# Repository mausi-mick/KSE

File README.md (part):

Kleiner , feiner  Kennlinienschreiber

Wozu braucht man einen Kennlinienschreiber ?

Reicht nicht ein Transistortester oder ein Voltmeter?
Für einen ersten Check ist ein Transistortester sehr hilfreich, zumal er auch den Typ des Transistors  und die Pin-Belegung ermitteln und anzeigen kann.

Aber die Ausgabewerte beziehen sich dabei nur auf einen Arbeitspunkt (Kollektorstrom).
Für den Schaltungsentwickler ist es aber oft wichtig, wie sich das Bauteil an verschiedenen
Arbeitspunkten – z.B. Basisströmen – verhält.

Worin unterscheidet sich der hier vorgestellte Kennlineinschreiber von anderen?

    • kompakter Aufbau:                                                                                                 Abmessungen: 8x9x6cm (lxbxh),  Gewicht: < 500 g (inkl. 18650 Lio-Akku).
    • unabhängig von externer Stromversorgung (Akku Betrieb,mit einer 18650 Zelle)
    • ausgelegt für bipolar Transistoren/Dioden, MosFets, J-Fets(incl. Depl.Mode MosFets).
    • Kollektor/Emitterspannung < 12V , 0 ..150mA  optimal für Kleinleistungstransistoren
    • Basisstrom von ca 5µA ... 1000µA mit präziser Konstant-Stromquelle, 
    • Gatespannung  100 mV ...12 V in 100 mV Schritten (änderbar), 
    • einstellbare Strombegrenzung (z.B. Dioden 5mA, 50mA,…)
    • relativ grosses Farbdisplay (3.2“)
    • einfache und schnelle Eingabe über Dreh-Encoder an Interrupt-Pins
    • hohe Genauigkeit und klare Kennlinien dank 12 bit ADC’s / DAC’s
    • diverse Skalen für x (U) und y-(I) Achse : detaillierte Darstellung interessanter Bereiche
    • Direkter Vergleich von Kennlinien (Typen gleicher Polarität oder Komplementärtyp)
    • Anzeige von typischen Werten wie Beta(Ib), V-Threshold,V-Pinch, Idss
    • Bluetooth Schnittstelle (BLE 4.0) für Datentransfer zum PC bzw. Smartphone/ Tablet
    • Datentransfer über USB zur Darstellung der Kurven auf PC mit z.B. Processing.
    • Speichern der Eingabeparameter im internen EEPROM
    • geringer Stromverbrauch: Uce (15V) erst bei Messvorgang zugeschaltet. 
    • Zusatzfunktion: einstellbare  Konstantspannungsquelle 1 mV  bis 12, 00V,> 10 mA
    • Zusatzfunktion: einstellbare Konstanstromquelle von 1µA bis 4000 µA
    • Zusatzfunktion: Treppenstufengenerator für niedrige Frequenzen +4V, ...0V (...-4V) 
    • untergebracht auf 5 Platinen (Kicad) einlagig 
    • relativ niedrige Bauteilkosten

Dieser Kennlinienschreiber basiert auf dem sehr interessanten und gut dokumentierten Projekt von Peter Balch : Transistor Curve Tracer [1], aus dem auch u.a. die Grafik-library leicht modifiziert übernommen wurde.

Ich habe mich dann aber doch ziemlich  - auch vom Konzept her - weit davon entfernt, um eine bessere und rauschärmere Darstellung hinzubekommen mit einem deutlich erweiterten Messbereich ,einer einfachen Bedienung und erweiterter Funktionalität, was sich leider auch im Preis niederschlägt. 
Ich habe die bisherige Bedienung über das Touchpanel eliminiert und mache die Programmsteuerung und Parameteränderungen über zwei Drehencoder, die an den beiden ext. Interrupt-Pins des NANO hängen und so eine schnelle Reaktion ermöglichen. Die Eingabe ist hiermit – gerade bei dem kleinen Display und den vielen Parameterwerten – wesentlich angenehmer und schneller als per Touch. 

Der Nachbau ist wegen einiger SMDs  und der Verdrahtung einiger Platinen  komplexer und daher nicht unbedingt für „Anfänger“ geeignet. Bei einigen Spezial-ICs ist/war auch mit erheblichen Beschaffungszeiten (in Deutschland) zu rechnen.

Basis ist ein Arduino-NANO(Clone), am besten mit vorinstalliertem Opti-Boot Loader [2,3,4], da man dort 1.5 kB mehr freien Flash-Speicher hat, ansonsten hat man nur einige 100 Byte Flash frei.

Anmerkung:
 ATMega328 Board mit vorinstalliertem Opti-Boot-Loader: 
 z.B. Arduino-UNO, Adafruit Metro Mini 328,  oder ein Board mit mehr Flash und Port-Pins (für Erweiterungen): ATMega2560 ).

Anmerkung:
Auch das UNO-Board oder Adafruit Metro-Mini sind hier verwendbar, da ich die zusätzlichen rein analogen Pins des NANO (A6,A7) nicht benutze.

Das Adafruit-Board Metro Mini 328 hat neben der besseren Anordnung der Pins (alle digit.Pins und somit auch Pin13 (SPI-SCK)  auf einer Seite) auch die Möglichkeit, durch eine Lötbrücke die Pegel auf 3.3V zu setzen, sodass man für das Display und das HM-10 BLE-Modul keine Spannungsteiler zur Pegelanpassung benötigt.

Der Mikroprozessor steuert zwei 12bit-DACs (im MCP4822 SPI) für die Uce Versorgung , ausserdem für die Basis/Gate-Ansteuerung einen 12 bit DAC (MCP4725-I2C) an, der über einen DC/DC-Wandler (5 V → 30V) und für den I2C Bus über einen ADUM1250/51 isoliert betrieben wird.  

Dieser total isolierte DAC (Bereich von 1µA bis 4mA, 1µA Schritte, hier nur von 5µA bis 1200µA genutzt für die bipol. Transistoren genutzt) erzeugt den Basisstrom bzw. die Gate-Spannung in der – zum Bauteil / „device“ - passenden Polarität über eine Präzisionskonstantstromquelle.
 
Zugeschaltet wird der Basisstrom (bzw. die Gatespannung)  über elekronische Schalter („Photomos-Relais“) mit niedrigem On-Widerstand und Leckstrom (z.B. TLP222A ).

Neben diesen DACs wird auch ein 12-bit ADC (MCP3402 SPI) zur Messung der Collector-EmitterSpannung und zur am Messwiderstand RS (50 Ohm) abfallenden Spannung (zur Ermittlung des Collector-Stroms) verwandt. Er dient auch zur Überwachung der Akku-Spannung.
Momentan werden nur 3 von den 4 Eingängen des ADC’s genutzt.

Ausserdem versorgt der NANO das bis zu 3.2 Zoll grosse Farb-Display (ILI9341) (an SPI-Bus).

Probleme gab es mit den 4 SPI-Devices wegen der unterschiedlichen Geschwindigkeit, da das Display mit 8 MHz läuft, die DAC’s mit 3.6 MHz und der ADC aber nur mit 2 MHz                      (und der Touch noch langsamer, wird aber in dieser Version nicht genutzt).

Als realisierbare / nicht ganz perfekte Lösung speichere ich maximal 320-Messwerte pro eingestelltem Basisstrom in einer Tabelle mit SPI-Speed 2 MHz ab.
Anschliessend erhöhe ich die SPI-Speed auf 8MHz für das Display und
 gebe die Tabellenwerte auf dem Display aus, um dann wieder – mit reduzierter SPI-Speed - die nächsten 320 Messwerte zum nächsten Basisstrom zu speichern.

Die Spannung Uc wird über die beiden DACs des MCP4822 erzeugt, wobei DAC-B nur
die Werte (0V, 2V,4V ...10V) am Opamp TCA0372 ausgibt,
DAC-A erzeugt die Zwischenwerte von 0.0mV, 0.5mV, 1.0mV.,..2000mV.
Sie werden dann zu den aus DC-B erzeugten Werten addiert (zwei invertierende Verstärker hintereinandergeschaltet) , sodass insgesamt der Bereich von
0V bis 12V in 0.5mV – Schritten mit sehr guter Linearität erzeugt werden kann.
Diese Auflösung ist zwar etwas übertrieben, bei kleinen Spannungswerten (z.B. Kennlinie von Shottky-Dioden oder im Anfangsbereich der Kurven von bipolar bzw. Feldeffekttransistoren) bringt das aber was, auch wird durch eine Art „Oversampling“ der Mittelwert der Messungen zum gleichen x_Wert gebildet

Der Summierverstärker TCA0372 mit Verstärkung +1 für DAC_A und Verstärkung +10 für DAC_B ist in Abbildung 1 skizziert.
Da der TCA0372 kein Rail-to Rail Vertärker ist, benötigt er eine negative Hilfsspannung: 
 aus den +15V wird mithilfe eines kleinen Spannungswandlers (LMO78-5-.5 )  -5V erzeugt. 
Damit erhält man auch in Nullpunktsnähe saubere Kurven, gerade die 1, 2, 3V Skalen profitieren davon.

Stromversorgung

Versorgt wird der Kennlinienschreiber aus einer einzelnen Lion-Akku-Zelle (18650).
Es werden zwei Spannungen benötigt:
   5V für  Adafruit Metro mini bzw. 7,5V Arduino NANO) , an der auch das Diplay und die KonstantStromquelle hängen, und ca.
 15V zur Versorgung des TCA0372-Verstärkerboards (Uce).

Die zuerst untersuchte Lösung mit zwei MT3608 Modulen funktionierte stabil nur für die 15V Versorgung, bei der Microprocessorversorgung brach die Spannung bereits bei einer Akkuspannung von 3.9V ein.

Die Qualität der MT3608-Module  – neben der riskanten Inbetriebnahme (siehe unten) – ist aber sehr unterschiedlich, sodass ich auch eher andere Module verwenden würde.
Die ICs MT3608, SDB628 und SX1308 scheinen – auch vom Datenblatt – identisch zu sein.
Aber die Module haben unterschiedliches Layout und wohl auch unterschiedliche Bestückung.

Die Kondensatoren C1 C2 sollten 22µF haben, bei den von mir untersuchten Modulen lagen sie 
unter 10 µF.

Es funktioniert sehr gut mit einem kleinen SX1308-Modul, bei dem bei mir aber ein SDB628 StepUp-Wandler IC aufgelötet war. 

Das Modul ist ähnlich wie das MT3608-Modul aufgebaut, aber
niederohmiger: 
10 k anstelle 100k Trimmer und 200 Ohm gegen Masse anstelle 2.2k. [9]

Es ist bei 15V mit mehr als 150mA belastbar und funktioniert bereits ab ca 2.7 V.
Es ist auch für die 5V / 7,5V Vesrorgung sehr gut geeignet.

Für die 5 bzw. 7.5V verwende ich momentan ein kleines Modul mit festen Spannungswerten  (5V,8V,9V,12V). Es ist wohl ein SDB628 verbaut ( identisch mit MT3608 / SX1308?)  das Modul funktioniert sogar  bis unter 3V Eingansspannung. [10]

Anmerkung MT3608:
Etwas kritisch ist die Einstellung/Inbetriebnahme, da der Schleifer des 10-Gang-Trimmers direkt mit dem FB (Feedback-Pin 3)  verbunden ist und - am oberen Anschlag  -  die Ausgansspannung direkt mit FB  verbunden ist, der wohl nur 0.6V ? verträgt.
Man sollte also vor Anlegen der Eingansspannung den Regler mit ein einigen Umdrehungen aus der oberenAnschlagsposition bringen (und zwar nach höheren Ausgansspannungswerten , d.h. nach links drehen   chinesische Logik ??)   [5,6],

Um Energie zu sparen, wird die 15V Versorgung erst aktiviert, wenn die Kurven aufbereitet werden.
Die 7.5V / 5V  stehen nach Einschalten für das Microprocessor Board gleich zur Verfügung, an dem u.a.  das Display und die Konstanstromquelle hängen, die aber weniger als 1W benötigt.

Beim Einschalten sind die Ströme - auch wegen der Kondensatoren - deutlich höher.

Das Adafruit Board braucht wegen eines besseren LD-Reglers , auch reichen hier 5V am  herausgeführten USB-Eingang.
9],[10],[11]

Testen von Bauteilen

Nach diesem technischen Überblick mal etrwas mehr zum Test-Ablauf:

Nach dem Einschalten erscheint auf dem Display der Startbildschirm , auf dem an der linken Seite nur drei grosse Icons  aufleuchten mit Auswahlfeldern (Buttons) für:
    •  bipolar Transistoren (inclusive Dioden)
    •  Mosfets
    •  Junction-Fets (incl. n-Depletion-Mode-Mosfets)
      
die über einen Drehencoder angesteuert werden.
Die Aktivierung einer Schaltfläche erfolgt durch Drehen des 2. Encoders.
Daraufhin werden im oberen Bereich zwei Schaltflächen („P“ bzw „N“) zum Starten des Messvorgangs angezeigt, vorher sollte man aber die unterhalb in zwei Spalten dargestellten Parameter begutachten  und eventuell modifizieren.
Im mittleren Display Bereich an der linken Seite  die Parameter: 

    •  min:   minimaler Wert (Basisstrom bzw. Gatespannung), mit dem der Messvorgang gestartet werden soll
    •  incr: Schrittweite, mit der Basisstrom bzw. Gatespannung erhöht werden soll
    •  max:  maximal datzustellende  Basisstrom bzw. Gatespannungs-Kurve

Die Basisströme werden in µA eingetragen, die Gatespannung in 100mV Schritten.
 Von einer Diode wird dann ausgegangen, wenn bei  „bipolar“ das Feld  incr: auf 0 gesetzt wird.

Am rechten Rand des Displays werden folgende Parameter angezeigt:

    •   Bluet/CCS: Transfer der Daten mit BLE 4.0 an PC bzw Smartphone,  bzw.    Konstantspannungs-Konstantspannungs-Betrieb
    •   x-scale[V]:    Länge der x-Skala  ( 1V,  2V,  3V,  4V,  6V,  12V)
    •   y-scale[mA]  Höhe   der y-Skala ( 2 mA, 5 mA, 10 mA, 20 mA, 50 mA, 100 mA)
Anmerkung: 
 Feld Bluet/CCS = 0         Ausgabe der Kennliniendaten 
                            = 1        Ausgabe der Kennliniendaten auch über Bluetooth an Smartphone etc. 
                            = 2        Umschalten auf Konstantspannungsquellen-Betrieb
                            = 3        Umschalten auf  Konstantstromquellen-Betrieb   
                            = 4,5 ,6 Treppenstufengenerator. 
                            
Die Verwaltung der Parameter erfolgt ähnlich wie beim Startbildschirm beschrieben, zwischen den Feldern springt man durch Drehen des Encoders 2, Auswahl eines Paramters durch mit dem anderen Encoder, ändern der Parameter duch Encoder-Drehung, Speichern/Verlassen des Parameters durch den andren Encoder.

Ist man mit den Einstellungen zufrieden, startet man den Messvorgang / Kurven durch Positionieren mit dem  Encoder auf Feld „P“  (für p-Devices) bzw. “N“ (für n-Devices)  
Hier hat man eine geringe Wartezeit zum Aktivieren, in der man nochmals die Parameter prüfen sollte. In dieser Wartephase blinken die aktivierten Felder P  bzw N. Durch drehen des anderen Encoders startet man dann den Messvorgang.

Erst jetzt sieht man die ausgewählten Skalen und im oberen Bereich das ausgewählte Device inclusive Icon.

Die Kurven werden vom x-y-0-Punkt aufgebaut und zusätzliche Daten (wie z.B. beta/hfe beim npn/pnp und der Basisstrom/Gatespannung )  am Ende der Kurven eingetragen.

Am Ende der Messung bleibt der Bildschirm mit den dargestellten Kurve stehen und es erscheint links oben eine Anfrage / Aufforderung in zeitlichem Abstand :

    •   ob man die Messung beenden will  („Stop ?“)
    •   ob man die Messung fortsetzen will mit geänderten Parametern  („Param ?“)
    •   ob man das gerade dargestellte Bauteil mit einem Bauteil gleicher Polarität vergleichen will („Compare ?“) 
    •   ob man das gerade dargestellete Bauteil mit einem Bauteil anderer Polarität vergleichen will („Complem. ?“)  (komplementär-Typ z.B. antiparallele Diode)

Die Auswahl erfolgt wieder durch Encoderdrehung zu dem gerade angezeigten Aufforderung.

Anmerkung:

Will man z.B. die Kennlinien von einem n-Device mit einem p-Device vergleichen, ermittelt man zuerst normal die Kennlinien des n-Devices, tauscht das n gegen das p-Device in der Textool Messfassung und startet den Vergleich 
durch Auswahl des Feldes „Complementary“ mit dem Encoder .

Es werden die Kennlinien des p-Devices zusätzlich in einer anderen Farbe auf dem Display dargestellt („Komplementärtyp“).

Vergleich von Komponenten gleicher Polarität erfolgt entsprechend 
durch Auswahl des Feldes „Compare“.

   Speicherung geänderter Parameter-im internen EEPROM

Die festgelegten Parameter werden beim Start der Kurven im internen EEPROM hinterlegt , 
sodass man auch beim Einschalten des Geräts die letzt eingegebenen Parameter angezeigt bekommt. 

Im EEPROM sind dafür folgende Adressen belegt:

    •   0: Transistor-Typ  0: bipolar,
    •   1: Bluetooth : 1=on, 0=off
    •   2: x-Skala: 1,2,3,4,6,12
    •   3 y-Skala: 2,5,10,20,50,100 mA
    •   4: minimaler Basisstrom bipolar-Transistor
    •   6: maximaler Basisstrom bipolar-Transistor 
    •   8: increment Basisstrom bipolar-Transistor 
    • 10: minimale Stepweite für Eingabe  min: ( Feld 4 )
    • 12: minimale StepWeite für Eingabe max: ( Feld 6 )
    • 14: minimale StepWeite für Eingabe incr:: ( Feld 8 )

    •   20: Transistor-Typ  1:  Mosfet
    •   21: Bluetooth : 1=on, 0=off
    •   22: x-Skala: 1,2,3,4,6,12
    •   23 y-Skala: 2,5,10,20,50,100 mA
    •   24: minimaler Gatespannung Mosfet
    •   26: maximaler GatespannungMosfet 
    •   28: increment Gatespannung Mosfet 
    •   30: minimale Stepweite für Eingabe  min: ( Feld 24 )
    •   32: minimale StepWeite für Eingabe max: ( Feld 26 )
    •   34: minimale StepWeite für Eingabe incr:: ( Feld 28 )

    •   40: Transistor-Typ  2:  J-Fet 
    •   41: Bluetooth : 1=on, 0=off
    •   42: x-Skala: 1,2,3,4,6,12
    •   43 y-Skala: 2,5,10,20,50,100 mA
    •   44: minimaler  Gatespannung J-Fet
    •   46: maximaler Gatespannung-J-Fet 
    •   48: increment  Gatespannung J-Fet 
    •   50: minimale Stepweite für Eingabe  min: ( Feld 44 )
    •   52: minimale StepWeite für Eingabe max: ( Feld 46 )
    •   54: minimale StepWeite für Eingabe incr:: ( Feld 48 )

Ausserdem kann man den Bauteil-Namen (z.B. BC548C  oder auch andere Informationen) im internen EEProm ab Adresse 100/101 hinterlegen: 

    •   100: Länge des Textfeldes 
    •   101: Text 1. Byte
    •   102: Text 2. Byte
    •  ...
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
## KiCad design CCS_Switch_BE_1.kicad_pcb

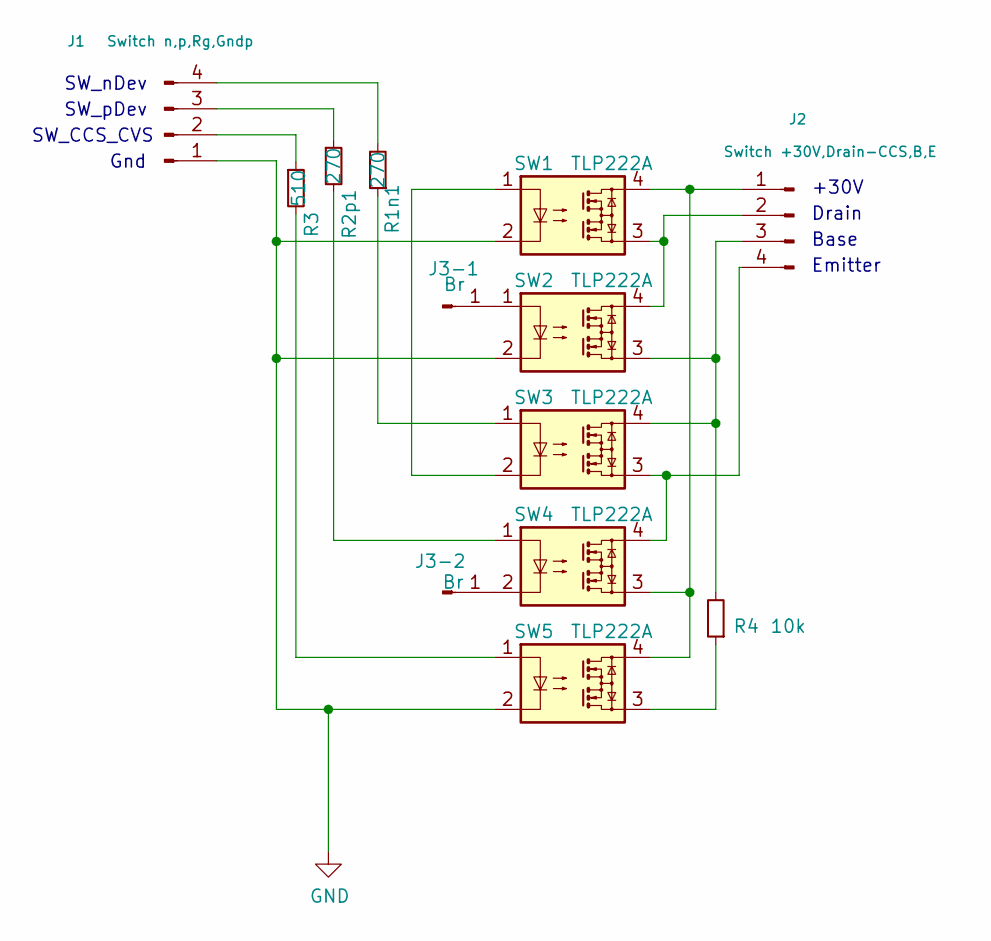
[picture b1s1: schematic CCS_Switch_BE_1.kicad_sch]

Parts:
J1: Switch n,p,Rg,Gndp; PinHeader_1x04_P2.54mm_Vertical
J2: Switch +30V,Drain-CCS,B,E; PinHeader_1x04_P2.54mm_Vertical
J3-1, J3-2: Br; PinHeader_1x01_P2.54mm_Vertical
R1n1, R2p1: 270; R_1206_3216Metric_Pad1.30x1.75mm_HandSolder
R3: 510; R_1206_3216Metric_Pad1.30x1.75mm_HandSolder
R4: 10k; R_Axial_DIN0207_L6.3mm_D2.5mm_P10.16mm_Horizontal
SW1, SW2, SW3, SW4, SW5: TLP222A; DIP-4_W7.62mm

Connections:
GND: J1.1, SW1.2, SW2.2, SW5.2
unnamed: J1.2, R3.1
unnamed: J1.3, R2p1.1
unnamed: J1.4, R1n1.2
unnamed: J2.1, SW1.4, SW4.3, SW5.4
unnamed: J2.2, SW1.3, SW2.4
unnamed: J2.3, R4.2, SW2.3, SW3.4
unnamed: J2.4, SW3.3, SW4.4
unnamed: J3-1.1, SW2.1
unnamed: J3-2.1, SW4.2
unnamed: R1n1.1, SW3.1
unnamed: R2p1.2, SW4.1
unnamed: R3.2, SW5.1
unnamed: R4.1, SW5.3
unnamed: SW1.1, SW3.2

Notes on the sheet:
Base
SW_pDev
SW_CCS_CVS
SW_nDev
+30V
Drain
Emitter
Gnd

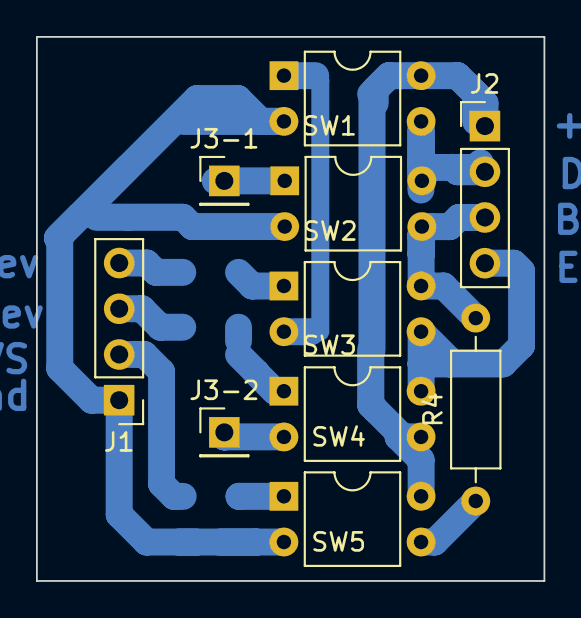
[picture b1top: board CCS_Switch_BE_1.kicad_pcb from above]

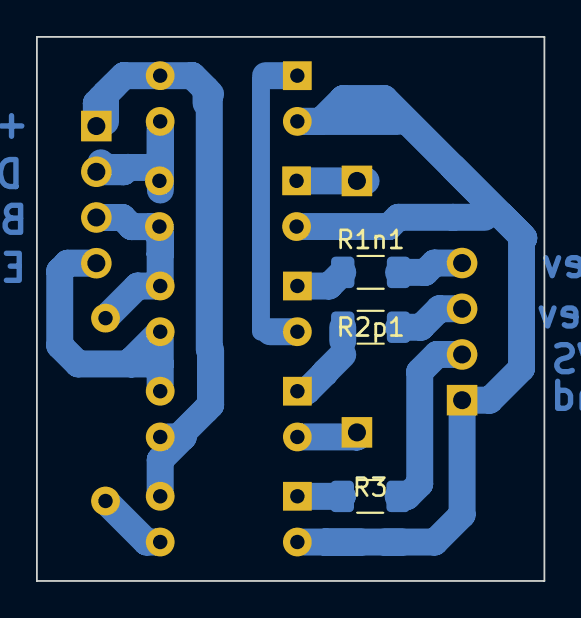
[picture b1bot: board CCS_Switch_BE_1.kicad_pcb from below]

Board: 2 copper layers, 28.2 x 30.2 mm, 13 parts (3 on the bottom side), 15 nets.

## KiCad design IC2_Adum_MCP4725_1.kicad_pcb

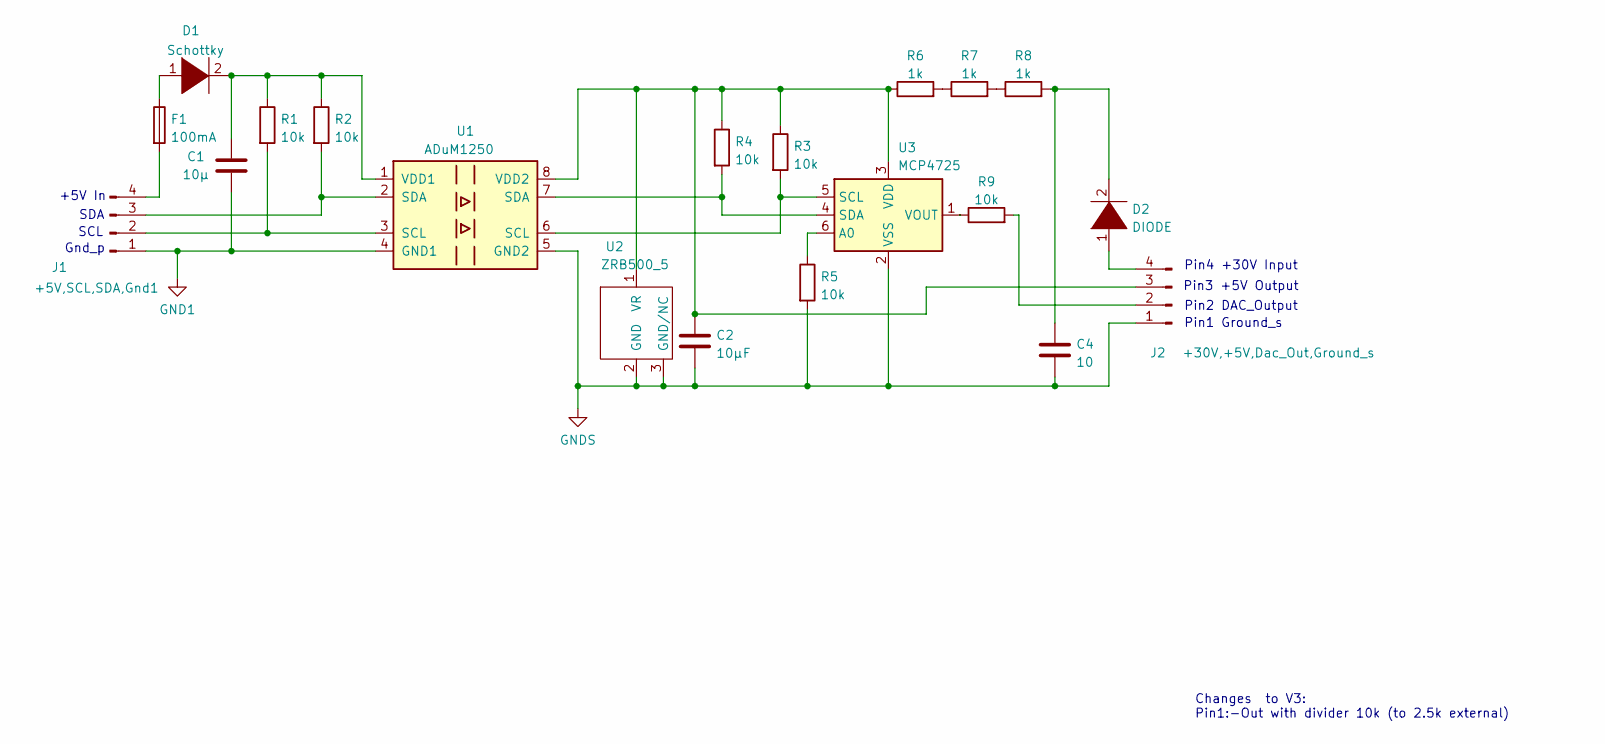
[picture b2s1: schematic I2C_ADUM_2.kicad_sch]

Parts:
C1: 10µ; C_1206_3216Metric_Pad1.33x1.80mm_HandSolder
C2: 10µF; C_1210_3225Metric_Pad1.33x2.70mm_HandSolder
C4: 10; C_1210_3225Metric_Pad1.33x2.70mm_HandSolder
D1: Schottky; D_1206_3216Metric_Pad1.42x1.75mm_HandSolder
D2: DIODE; D_0805_2012Metric_Pad1.15x1.40mm_HandSolder
F1: 100mA; Fuse_1206_3216Metric_Pad1.42x1.75mm_HandSolder
J1: +5V,SCL,SDA,Gnd1; PinHeader_1x04_P2.54mm_Vertical
J2: +30V,+5V,Dac_Out,Ground_s; PinHeader_1x04_P2.54mm_Vertical
R1, R2, R3, R4, R5, R9: 10k; R_1206_3216Metric_Pad1.30x1.75mm_HandSolder
R6, R7, R8: 1k; R_1206_3216Metric_Pad1.30x1.75mm_HandSolder
U1: ADuM1250; SOIC-8_3.9x4.9mm_P1.27mm
U2: ZRB500_5; SOT-23-3
U3: MCP4725; SOT-23-6

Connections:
GND1: C1.2, J1.1, U1.4 (GND1)
GNDS: C2.2, C4.2, J2.1, R5.2, U1.5 (GND2), U2.2 (GND), U2.3 (GND/NC), U3.2 (VSS)
unnamed: C1.1, D1.2 (A), R1.1, R2.1, U1.1 (VDD1)
unnamed: C2.1, J2.3, R3.1, R4.1, R6.1, U1.8 (VDD2), U2.1 (VR), U3.3 (VDD)
unnamed: C4.1, D2.2 (A), R8.2
unnamed: D1.1 (K), F1.1
unnamed: D2.1 (K), J2.4
unnamed: F1.2, J1.4
unnamed: J1.2, R1.2, U1.3 (SCL)
unnamed: J1.3, R2.2, U1.2 (SDA)
unnamed: J2.2, R9.2
unnamed: R3.2, U1.6 (SCL), U3.5 (SCL)
unnamed: R4.2, U1.7 (SDA), U3.4 (SDA)
unnamed: R5.1, U3.6 (A0)
unnamed: R6.2, R7.1
unnamed: R7.2, R8.1
unnamed: R9.1, U3.1 (VOUT)

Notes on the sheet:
Pin2 DAC_Output
Changes to V3: Pin1:-Out with divider 10k (to 2.5k external)
+5V In
Pin3 +5V Output
Gnd_p
SDA
Pin1 Ground_s
SCL
Pin4 +30V Input

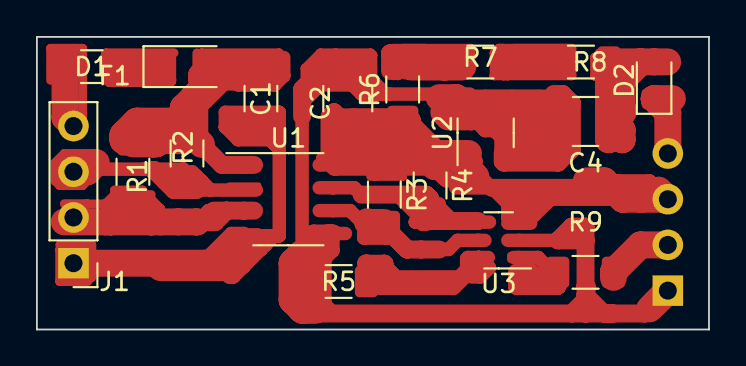
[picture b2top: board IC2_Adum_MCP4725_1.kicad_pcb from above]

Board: 2 copper layers, 37.3 x 16.3 mm, 20 parts (1 on the bottom side), 17 nets.

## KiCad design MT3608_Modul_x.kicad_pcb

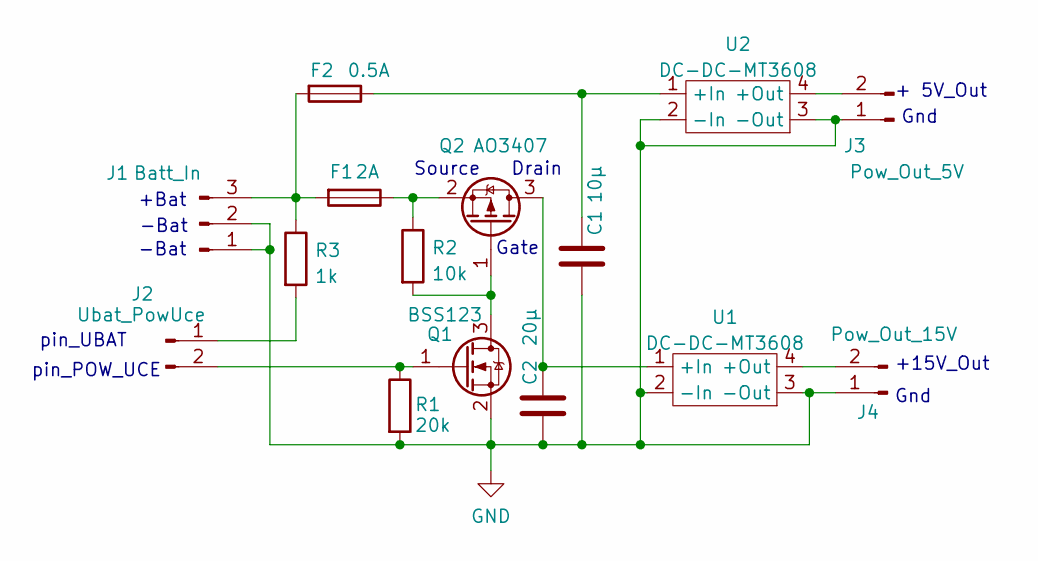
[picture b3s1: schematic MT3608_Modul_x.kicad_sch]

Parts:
C1: 10µ; C_1206_3216Metric_Pad1.33x1.80mm_HandSolder
C2: 20µ; C_1210_3225Metric_Pad1.33x2.70mm_HandSolder
F1: 2A; Fuse_1206_3216Metric_Pad1.42x1.75mm_HandSolder
F2: 0.5A; Fuse_1206_3216Metric_Pad1.42x1.75mm_HandSolder
J1: Batt_In; PinHeader_1x03_P2.54mm_Horizontal
J2: Ubat_PowUce; PinHeader_1x02_P2.54mm_Vertical
J3: Pow_Out_5V; PinHeader_1x02_P2.54mm_Vertical
J4: Pow_Out_15V; PinHeader_1x02_P2.54mm_Vertical
Q1: BSS123; SOT-23
Q2: AO3407; SOT-23
R1: 20k; R_1206_3216Metric_Pad1.30x1.75mm_HandSolder
R2: 10k; R_1206_3216Metric_Pad1.30x1.75mm_HandSolder
R3: 1k; R_1206_3216Metric_Pad1.30x1.75mm_HandSolder
U1, U2: DC-DC-MT3608

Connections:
GND: C1.2, C2.2, J1.1, J1.2, J3.1, J4.1, Q1.2 (S), R1.2, U1.2 (-In), U1.3 (-Out), U2.2 (-In), U2.3 (-Out)
unnamed: C1.1, F2.1, U2.1 (+In)
unnamed: C2.1, Q2.3 (D), U1.1 (+In)
unnamed: F1.1, Q2.2 (S), R2.1
unnamed: F1.2, F2.2, J1.3, R3.1
unnamed: J2.1, R3.2
unnamed: J2.2, Q1.1 (G), R1.1
unnamed: J3.2, U2.4 (+Out)
unnamed: J4.2, U1.4 (+Out)
unnamed: Q1.3 (D), Q2.1 (G), R2.2

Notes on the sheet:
Drain
pin_UBAT
-Bat
Source
+Bat
pin_POW_UCE
+15V_Out
Gnd
Gate
+ 5V_Out

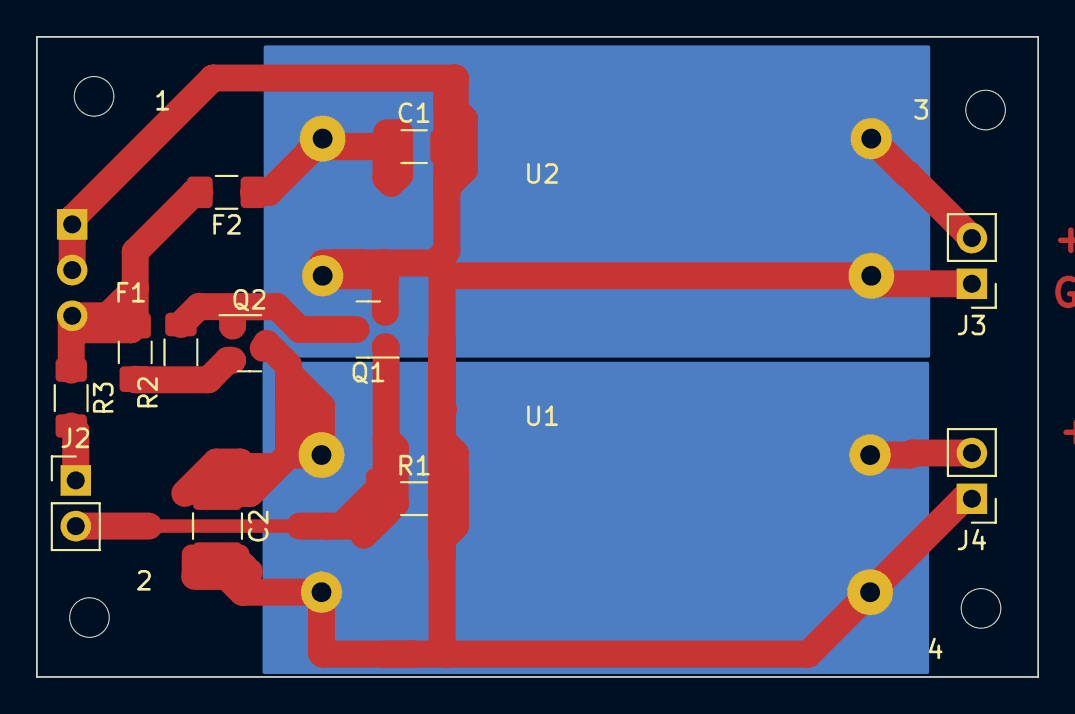
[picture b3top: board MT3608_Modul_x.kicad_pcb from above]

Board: 2 copper layers, 55.6 x 35.6 mm, 19 parts (1 on the bottom side), 10 nets.

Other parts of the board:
1, 2, 3, 4: MH_M2; MountingHole_2.2mm_M2

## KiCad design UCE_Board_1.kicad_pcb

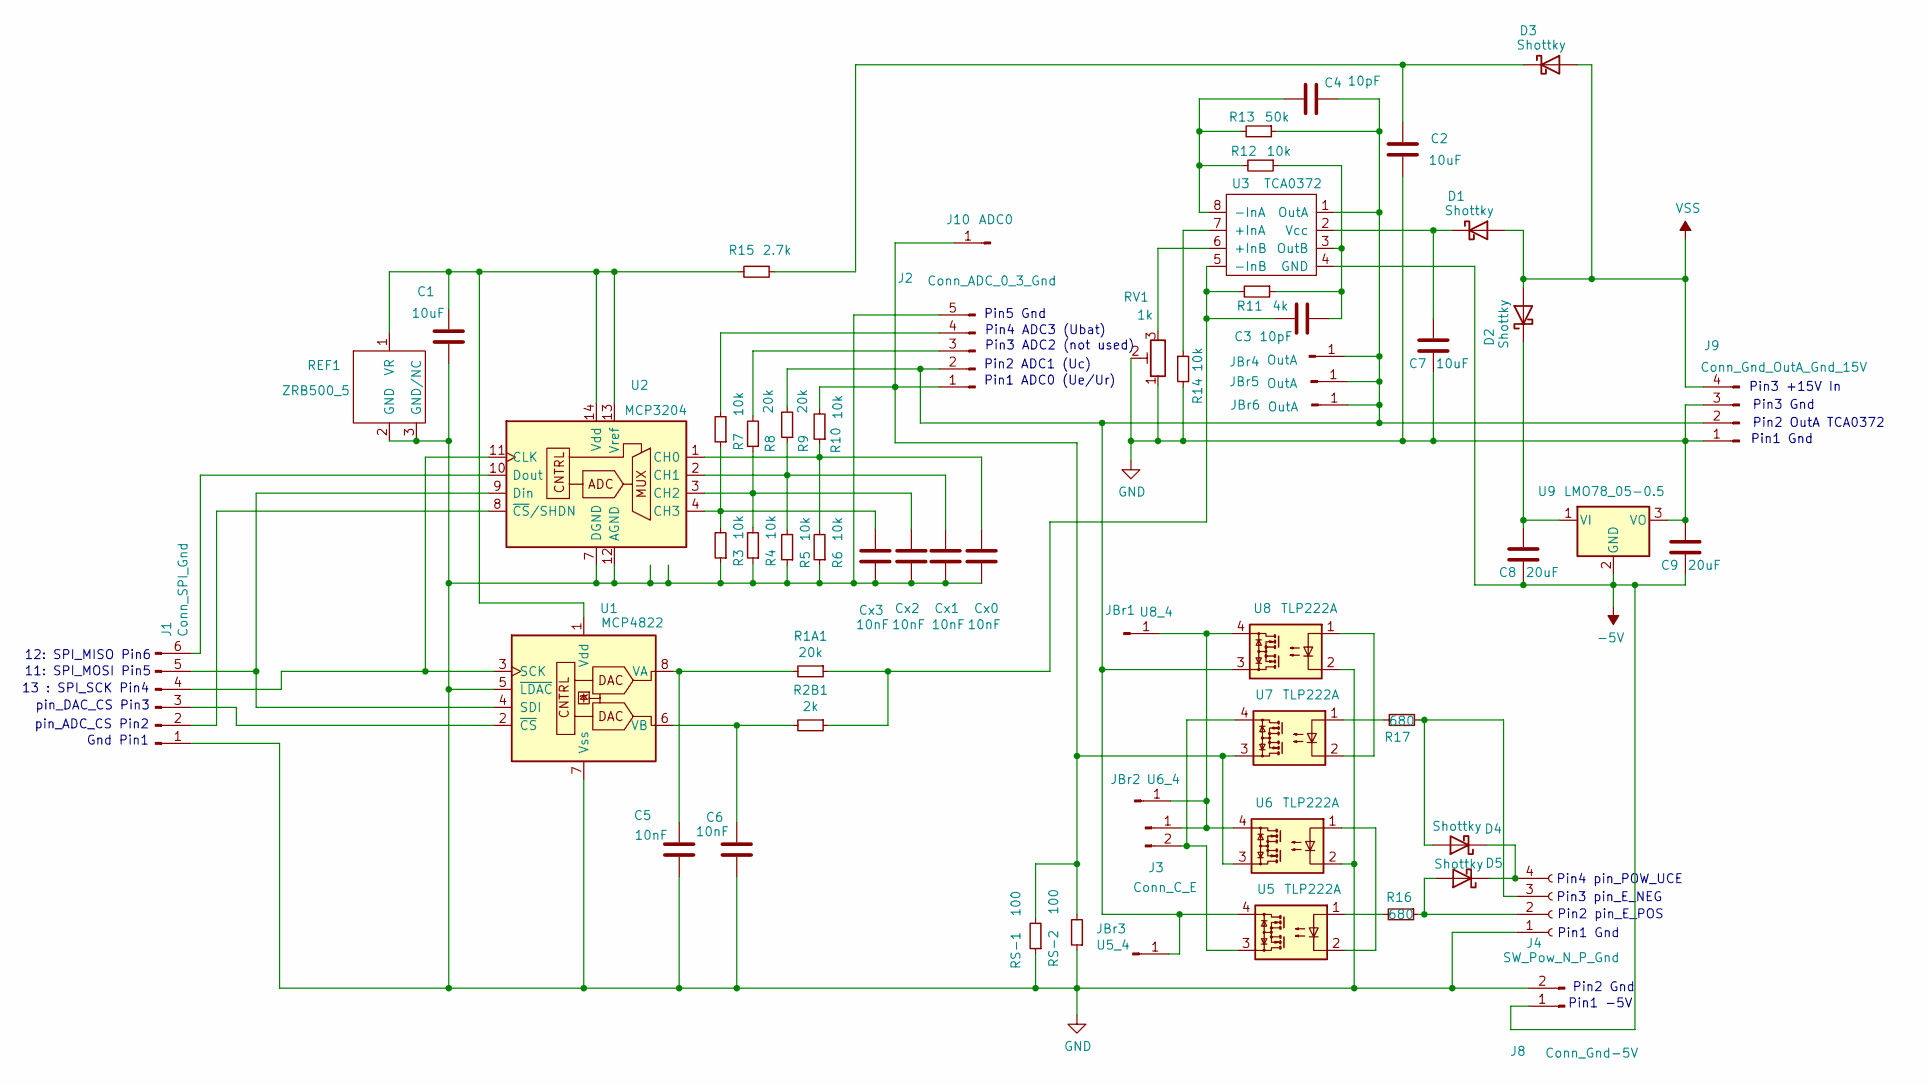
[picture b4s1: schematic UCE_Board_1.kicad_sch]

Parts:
C1: 10uF; C_1210_3225Metric_Pad1.33x2.70mm_HandSolder
C2: 10uF; C_1812_4532Metric_Pad1.57x3.40mm_HandSolder
C3: 10pF; C_Axial_L5.1mm_D3.1mm_P7.50mm_Horizontal
C4: 10pF; C_Axial_L3.8mm_D2.6mm_P7.50mm_Horizontal
C5, C6: 10nF; C_1206_3216Metric_Pad1.33x1.80mm_HandSolder
C7: 10uF; C_1206_3216Metric_Pad1.33x1.80mm_HandSolder
C8, C9: 20uF; C_1812_4532Metric_Pad1.57x3.40mm_HandSolder
Cx0, Cx1, Cx2, Cx3: 10nF; C_0805_2012Metric_Pad1.18x1.45mm_HandSolder
D1, D2, D3: Shottky; D_1206_3216Metric_Pad1.42x1.75mm_HandSolder
D4, D5: Shottky; D_0603_1608Metric_Pad1.05x0.95mm_HandSolder
J1: Conn_SPI_Gnd; PinHeader_1x06_P2.54mm_Horizontal
J2: Conn_ADC_0_3_Gnd; PinHeader_1x05_P2.54mm_Vertical
J3: Conn_C_E; PinHeader_1x02_P2.54mm_Horizontal
J4: SW_Pow_N_P_Gnd; PinHeader_1x04_P2.54mm_Horizontal
J8: Conn_Gnd-5V; PinHeader_1x02_P2.54mm_Vertical
J9: Conn_Gnd_OutA_Gnd_15V; PinHeader_1x04_P2.54mm_Horizontal
J10: ADC0; PinHeader_1x01_P2.54mm_Vertical
JBr1: U8_4; PinHeader_1x01_P2.54mm_Vertical
JBr2: U6_4; PinHeader_1x01_P2.54mm_Vertical
JBr3: U5_4; PinHeader_1x01_P2.54mm_Vertical
JBr4, JBr5, JBr6: OutA; PinHeader_1x01_P2.54mm_Vertical
R1A1, R8, R9: 20k; R_1206_3216Metric_Pad1.30x1.75mm_HandSolder
R2B1: 2k; R_1206_3216Metric_Pad1.30x1.75mm_HandSolder
R3, R4, R5, R6, R7, R10: 10k; R_1206_3216Metric_Pad1.30x1.75mm_HandSolder
R11: 4k; R_Axial_DIN0207_L6.3mm_D2.5mm_P10.16mm_Horizontal
R12: 10k; R_Axial_DIN0207_L6.3mm_D2.5mm_P10.16mm_Horizontal
R13: 50k; R_Axial_DIN0207_L6.3mm_D2.5mm_P10.16mm_Horizontal
R14: 10k; R_Axial_DIN0207_L6.3mm_D2.5mm_P15.24mm_Horizontal
R15: 2.7k; R_Axial_DIN0207_L6.3mm_D2.5mm_P10.16mm_Horizontal
R16, R17: 680; R_Axial_DIN0207_L6.3mm_D2.5mm_P10.16mm_Horizontal
REF1: ZRB500_5; SOT-23
RS-1, RS-2: 100; R_Axial_DIN0207_L6.3mm_D2.5mm_P10.16mm_Horizontal
RV1: 1k; Potentiometer_ACP_CA9-H2,5_Horizontal
U1: MCP4822; DIP-8_W7.62mm_LongPads
U2: MCP3204; DIP-14_W7.62mm
U3: TCA0372; DIP-8_W7.62mm_LongPads
U5, U6, U7, U8: TLP222A; DIP-4_W7.62mm
U9: LMO78_05-0.5; TO-220-3_Vertical

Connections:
-5V: C8.2, C9.2, J8.1, U3.4 (GND), U9.2 (GND)
GND: C1.2, C2.2, C5.1, C6.1, C7.2, C9.1, Cx0.1, Cx1.1, Cx2.1, Cx3.1, J1.1, J2.5, J4.1, J8.2, J9.1, J9.3, R3.1, R4.1, R5.1, R6.1, R14.2, REF1.2 (GND), REF1.3 (GND/NC), RS-1.1, RS-2.1, RV1.1, RV1.2, U1.5 (~LDAC), U1.7 (Vss), U2.5 (NC), U2.6 (NC), U2.7 (DGND), U2.12 (AGND), U6.2, U8.2, U9.3 (VO)
unnamed: C1.1, R15.2, REF1.1 (VR), U1.1 (Vdd), U2.13 (Vref), U2.14 (Vdd)
unnamed: C2.1, D3.1 (K), R15.1
unnamed: C3.1, R11.1, R12.1, U3.3 (OutB)
unnamed: C3.2, R1A1.1, R2B1.1, R11.2, U3.5 (-InB)
unnamed: C4.1, J2.2, J9.2, JBr3.1, JBr4.1, JBr5.1, JBr6.1, R9.2, R13.1, U3.1 (OutA), U5.4, U8.3
unnamed: C4.2, R12.2, R13.2, U3.8 (-InA)
unnamed: C5.2, R1A1.2, U1.8 (VA)
unnamed: C6.2, R2B1.2, U1.6 (VB)
unnamed: C7.1, D1.1 (K), U3.2 (Vcc)
unnamed: C8.1, D2.1 (K), U9.1 (VI)
unnamed: Cx0.2, R6.2, R10.1, U2.1 (CH0)
unnamed: Cx1.2, R5.2, R9.1, U2.2 (CH1)
unnamed: Cx2.2, R4.2, R8.1, U2.3 (CH2)
unnamed: Cx3.2, R3.2, R7.1, U2.4 (CH3)
unnamed: D4.1 (K), D5.1 (K), J4.4
unnamed: D4.2 (A), J4.3, R17.1
unnamed: D5.2 (A), J4.2, R16.1
unnamed: J1.2, U2.8 (~CS/SHDN)
unnamed: J1.3, U1.2 (~CS)
unnamed: J1.4, U1.3 (SCK), U2.11 (CLK)
unnamed: J1.5, U1.4 (SDI), U2.9 (Din)
unnamed: J1.6, U2.10 (Dout)
unnamed: J2.3, R8.2
unnamed: J2.4, R7.2
unnamed: J3.1, JBr1.1, JBr2.1, U6.4, U8.4
unnamed: J3.2, U5.3, U7.4
unnamed: J2.1, J10.1, R10.2, RS-1.2, RS-2.2, U6.3, U7.3
unnamed: R14.1, U3.7 (+InA)
unnamed: R16.2, U5.1
unnamed: R17.2, U7.1
unnamed: RV1.3, U3.6 (+InB)
unnamed: U5.2, U6.1
unnamed: U7.2, U8.1
VSS: D1.2 (A), D2.2 (A), D3.2 (A), J9.4

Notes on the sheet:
pin_ADC_CS Pin2
Pin1 Gnd
Pin5 Gnd
Gnd Pin1
Pin3 pin_E_NEG
Pin2 OutA TCA0372
Pin4 pin_POW_UCE
12: SPI_MISO Pin6
Pin2 ADC1 (Uc)
pin_DAC_CS Pin3
Pin2 pin_E_POS
Pin3 ADC2 (not used)
Pin2 Gnd
Pin1 ADC0 (Ue/Ur)
Pin3 +15V In
Pin1 -5V
Pin3 Gnd
11: SPI_MOSI Pin5
Pin4 ADC3 (Ubat)
13 : SPI_SCK Pin4

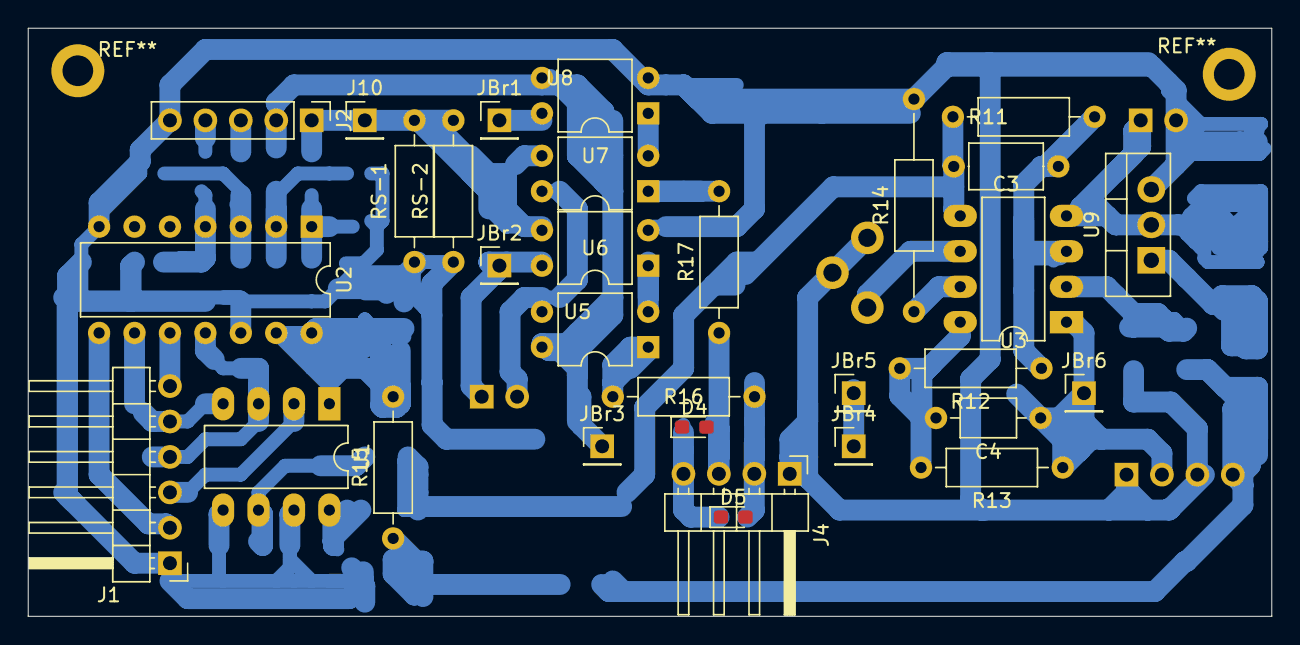
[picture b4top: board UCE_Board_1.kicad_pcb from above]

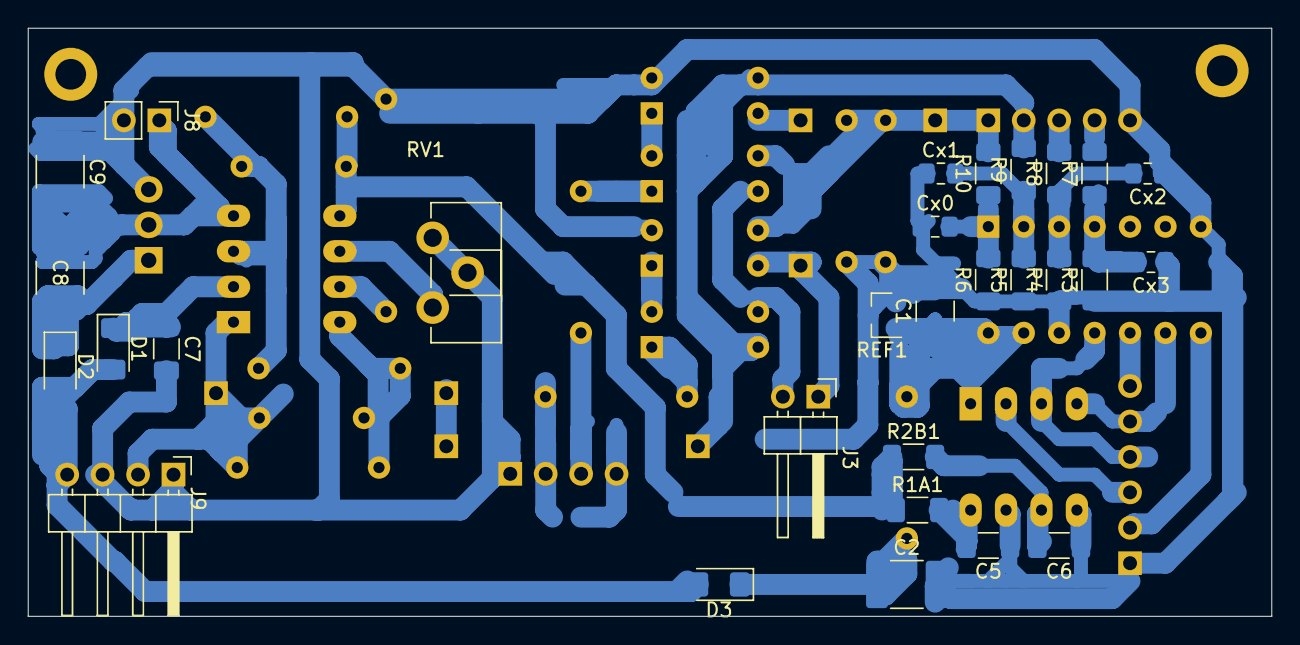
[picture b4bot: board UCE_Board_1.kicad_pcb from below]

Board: 2 copper layers, 89.2 x 42.2 mm, 60 parts (29 on the bottom side), 36 nets.

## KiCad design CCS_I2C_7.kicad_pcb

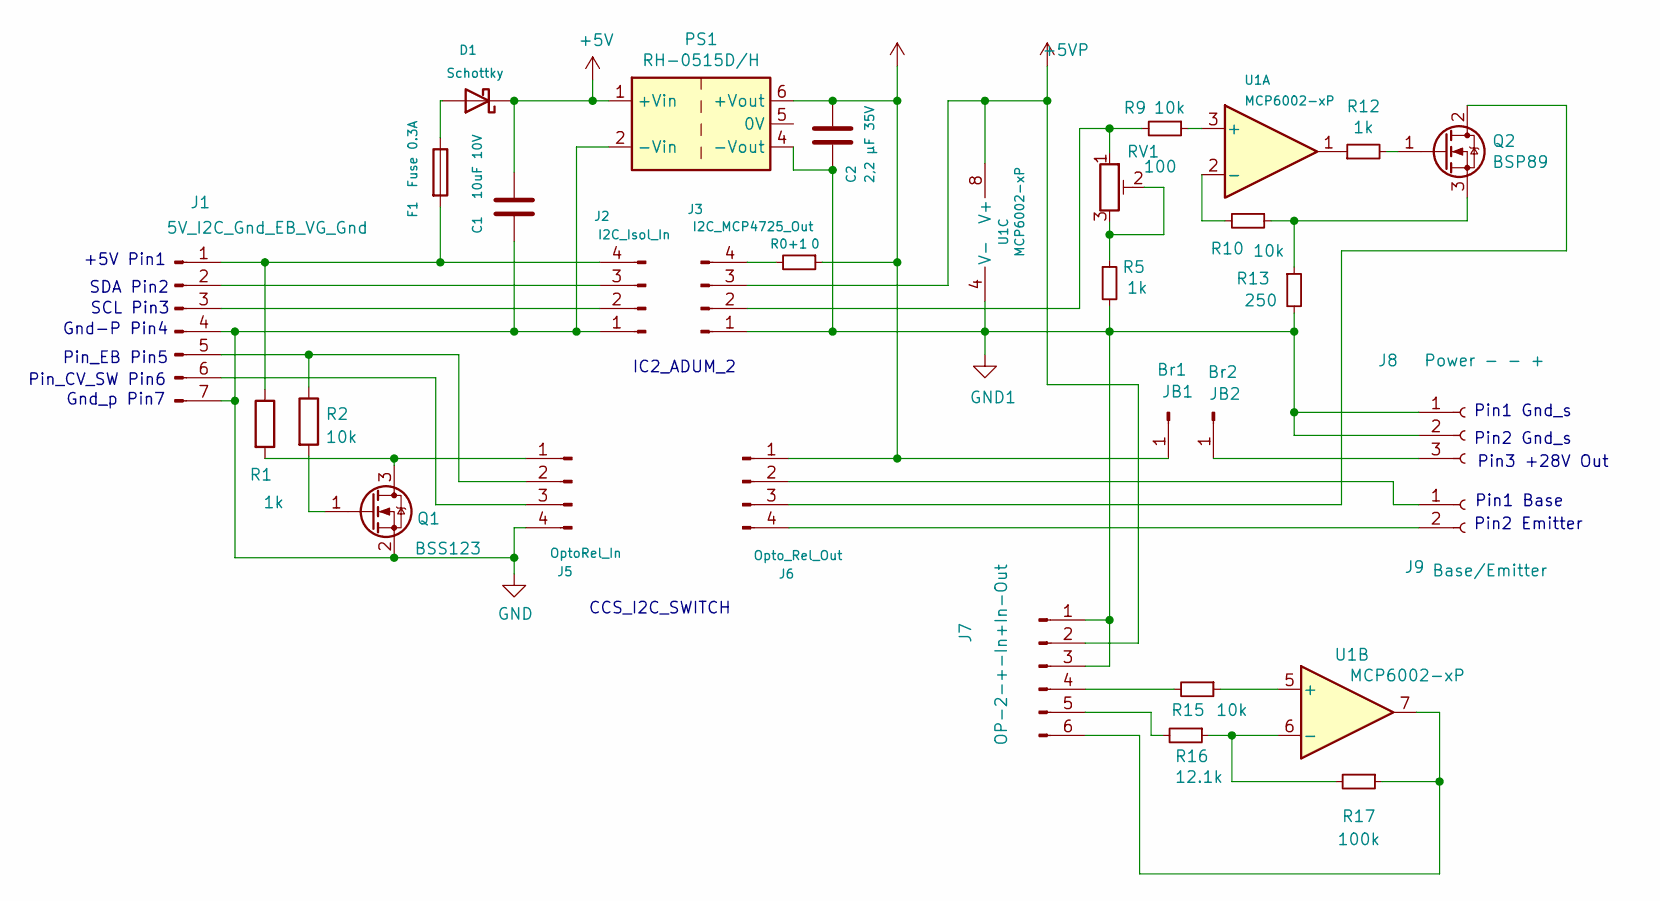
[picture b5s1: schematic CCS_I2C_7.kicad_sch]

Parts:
C1: 10uF 10V; C_1812_4532Metric_Pad1.57x3.40mm_HandSolder
C2: 2,2 µF 35V; C_1812_4532Metric_Pad1.57x3.40mm_HandSolder
D1: Schottky; D_1206_3216Metric_Pad1.42x1.75mm_HandSolder
F1: Fuse 0.3A; Fuse_1206_3216Metric_Pad1.42x1.75mm_HandSolder
J1: 5V_I2C_Gnd_EB_VG_Gnd; PinHeader_1x07_P2.54mm_Horizontal
J2: I2C_Isol_In; PinSocket_1x04_P2.54mm_Vertical
J3: I2C_MCP4725_Out; PinSocket_1x04_P2.54mm_Vertical
J5: OptoRel_In; PinSocket_1x04_P2.54mm_Vertical
J6: Opto_Rel_Out; PinSocket_1x04_P2.54mm_Vertical
J7: OP-2-+-In+In-Out; PinHeader_1x06_P2.54mm_Horizontal
J8: Power - - +; PinHeader_1x03_P2.54mm_Horizontal
J9: Base/Emitter; PinHeader_1x02_P2.54mm_Horizontal
JB1: Br1; PinHeader_1x01_P2.54mm_Vertical
JB2: Br2; PinHeader_1x01_P2.54mm_Vertical
PS1: RH-0515D/H; Converter_DCDC_XP_POWER-IHxxxxSH_THT
Q1: BSS123; SOT-23
Q2: BSP89; SOT-223-3_TabPin2
R0+1: 0; R_Axial_DIN0309_L9.0mm_D3.2mm_P12.70mm_Horizontal
R1: 1k; R_1206_3216Metric_Pad1.30x1.75mm_HandSolder
R2: 10k; R_1206_3216Metric_Pad1.30x1.75mm_HandSolder
R5, R12: 1k; R_Axial_DIN0207_L6.3mm_D2.5mm_P10.16mm_Horizontal
R9, R10, R15: 10k; R_Axial_DIN0207_L6.3mm_D2.5mm_P10.16mm_Horizontal
R13: 250; R_Axial_DIN0207_L6.3mm_D2.5mm_P10.16mm_Horizontal
R16: 12.1k; R_Axial_DIN0207_L6.3mm_D2.5mm_P10.16mm_Horizontal
R17: 100k; R_Axial_DIN0207_L6.3mm_D2.5mm_P10.16mm_Horizontal
RV1: 100; Potentiometer_ACP_CA6-H2,5_Horizontal
U1: MCP6002-xP; DIP-8_W7.62mm_LongPads

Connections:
+5V: C1.1, D1.1 (K), PS1.1 (+Vin)
+5VP: J3.3, J7.2, U1.8 (V+)
+28V: C2.1, J6.1, JB1.1, PS1.6 (+Vout), R0+1.1
GND: C1.2, J1.4, J1.7, J2.1, J5.4, PS1.2 (-Vin), Q1.2 (S)
GND1: C2.2, J3.1, J7.1, J7.3, J8.1, J8.2, PS1.4 (-Vout), R5.2, R13.2, U1.4 (V-)
unnamed: D1.2 (A), F1.1
unnamed: F1.2, J1.1, J2.4, R1.1
unnamed: J1.2, J2.3
unnamed: J1.3, J2.2
unnamed: J1.5, J5.2, R2.1
unnamed: J1.6, J5.3
unnamed: J3.2, R9.2, RV1.1
unnamed: J3.4, R0+1.2
unnamed: J5.1, Q1.3 (D), R1.2
unnamed: J6.2, J9.1
unnamed: J6.3, Q2.2 (D)
unnamed: J6.4, J9.2
unnamed: J7.4, R15.2
unnamed: J7.5, R16.2
unnamed: J7.6, R17.1, U1.7
unnamed: J8.3, JB2.1
unnamed: Q1.1 (G), R2.2
unnamed: Q2.1 (G), R12.2
unnamed: Q2.3 (S), R10.1, R13.1
unnamed: R5.1, RV1.2, RV1.3
unnamed: R9.1, U1.3 (+)
unnamed: R10.2, U1.2 (-)
unnamed: R12.1, U1.1
unnamed: R15.1, U1.5 (+)
unnamed: R16.1, R17.2, U1.6 (-)

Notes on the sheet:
Pin_EB Pin5
IC2_ADUM_2
+5V Pin1
Gnd-P Pin4
SDA Pin2
Pin2 Gnd_s
Pin3 +28V Out
SCL Pin3
Pin2 Emitter
Gnd_p Pin7
Pin1 Gnd_s
Pin1 Base
CCS_I2C_SWITCH
Pin_CV_SW Pin6

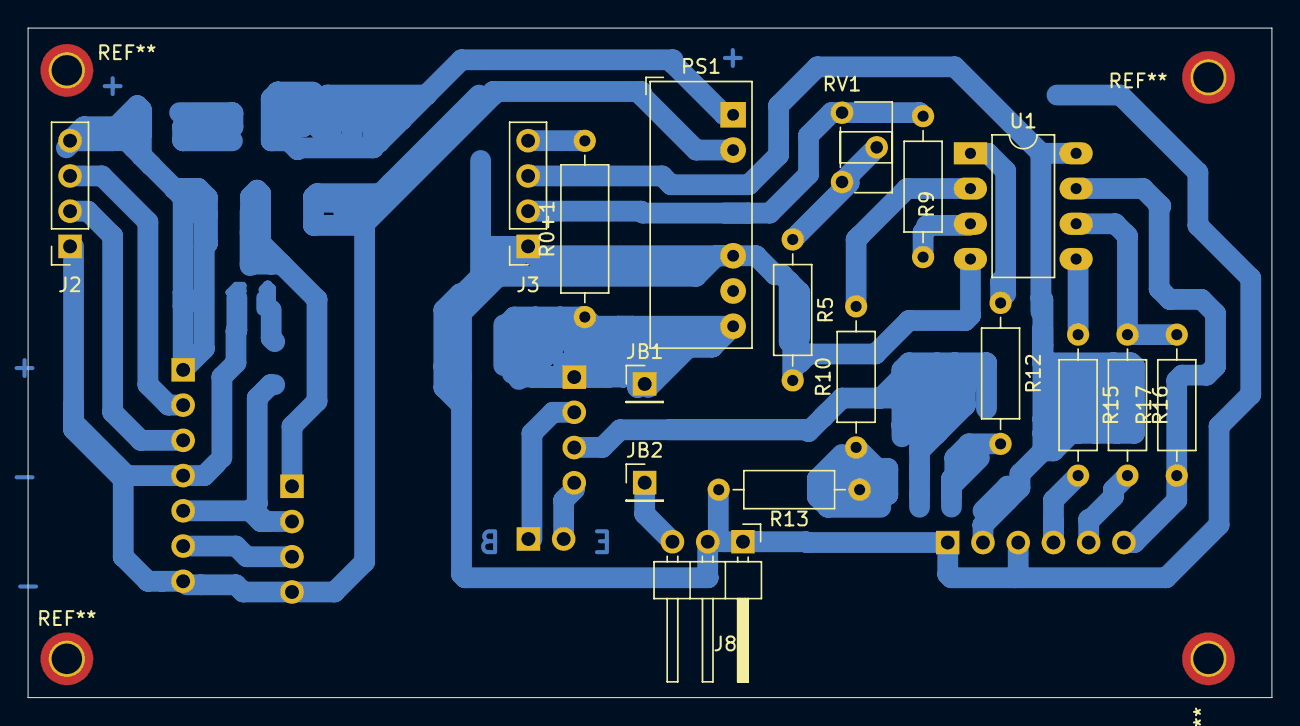
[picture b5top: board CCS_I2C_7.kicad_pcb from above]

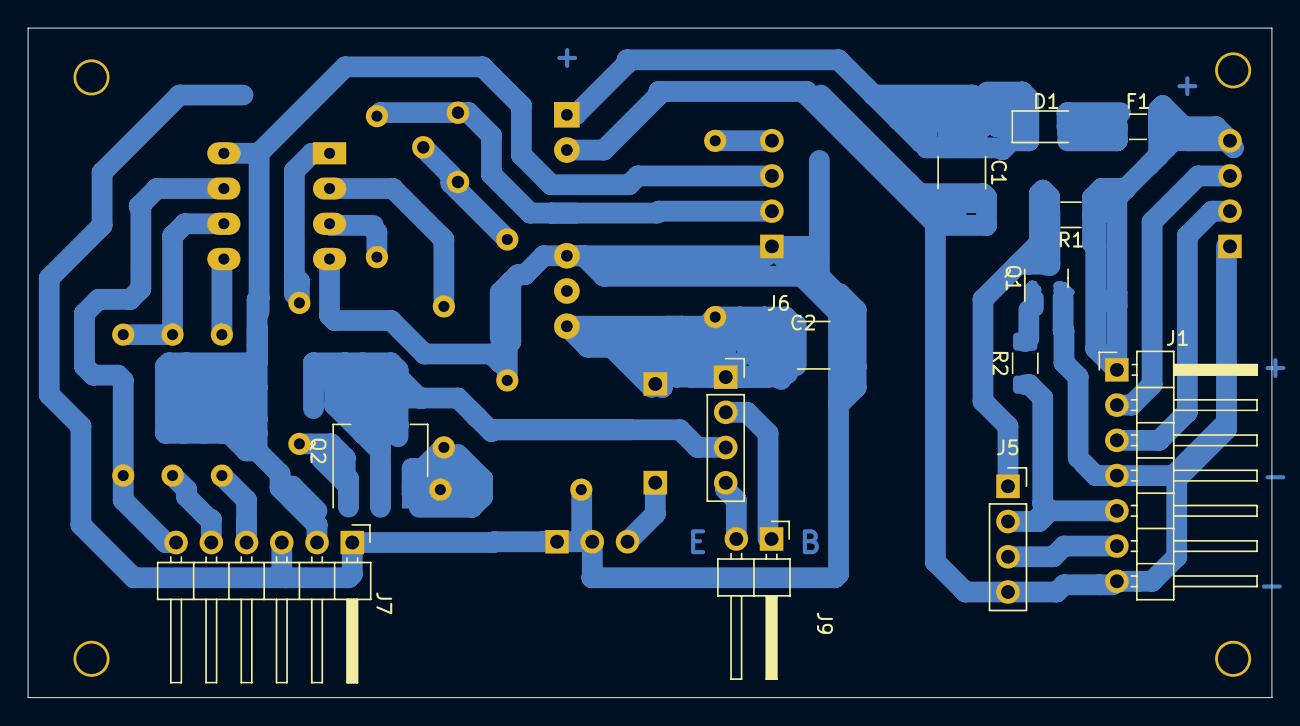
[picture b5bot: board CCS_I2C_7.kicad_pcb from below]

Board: 2 copper layers, 89.7 x 48.3 mm, 30 parts (13 on the bottom side), 30 nets.
